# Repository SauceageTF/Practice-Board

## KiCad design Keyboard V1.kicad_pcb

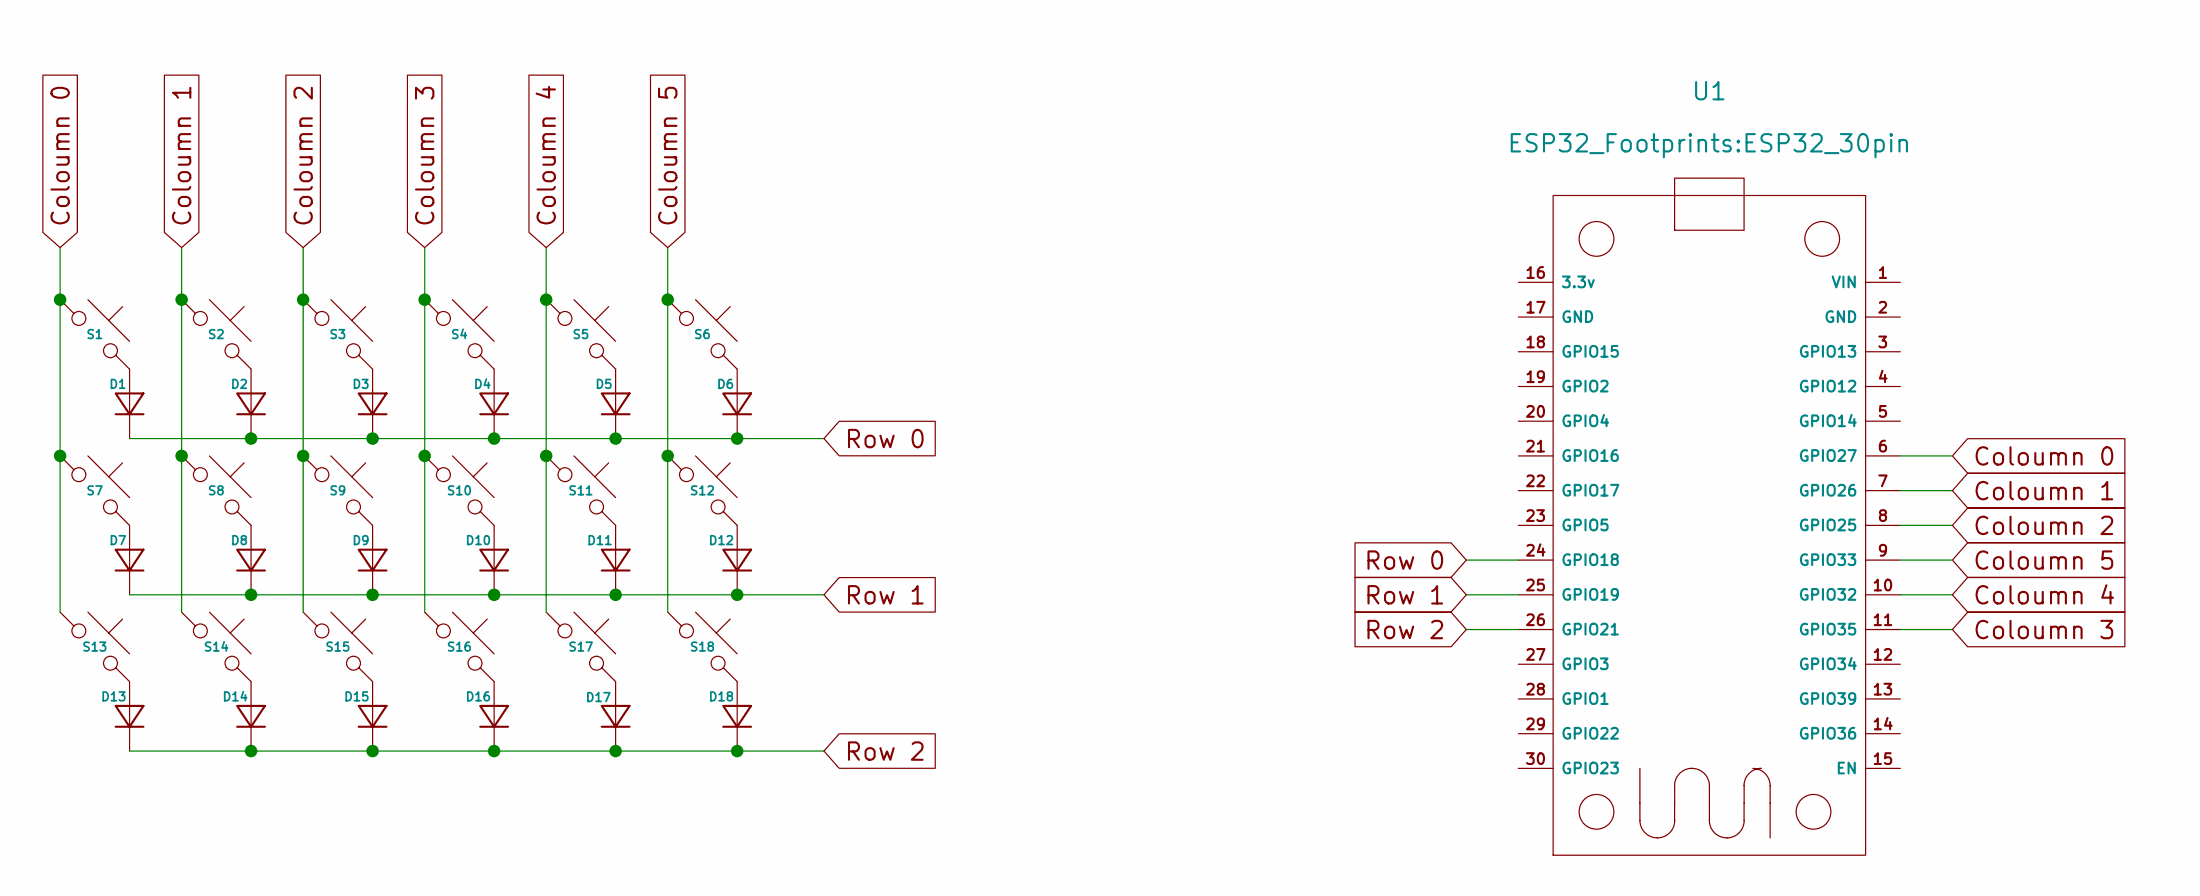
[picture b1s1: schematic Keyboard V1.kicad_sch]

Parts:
D1, D2, D3, D4, D5, D6, D7, D8, D9, D10, D11, D12, D13, D14, D15, D16, D17, D18: Diode_DO-35
S1, S2, S3, S4, S5, S6, S7, S8, S9, S10, S11, S12, S13, S14, S15, S16, S17, S18: MX_PCB_1.00u
U1: ESP32_30pin

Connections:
Coloumn 0: S1.1, S7.1, S13.1, U1.6 (GPIO27)
Coloumn 1: S2.1, S8.1, S14.1, U1.7 (GPIO26)
Coloumn 2: S3.1, S9.1, S15.1, U1.8 (GPIO25)
Coloumn 3: S4.1, S10.1, S16.1, U1.11 (GPIO35)
Coloumn 4: S5.1, S11.1, S17.1, U1.10 (GPIO32)
Coloumn 5: S6.1, S12.1, S18.1, U1.9 (GPIO33)
unnamed: D1.2 (A), S1.2
unnamed: D2.2 (A), S2.2
unnamed: D3.2 (A), S3.2
unnamed: D4.2 (A), S4.2
unnamed: D5.2 (A), S5.2
unnamed: D6.2 (A), S6.2
unnamed: D7.2 (A), S7.2
unnamed: D8.2 (A), S8.2
unnamed: D9.2 (A), S9.2
unnamed: D10.2 (A), S10.2
unnamed: D11.2 (A), S11.2
unnamed: D12.2 (A), S12.2
unnamed: D13.2 (A), S13.2
unnamed: D14.2 (A), S14.2
unnamed: D15.2 (A), S15.2
unnamed: D16.2 (A), S16.2
unnamed: D17.2 (A), S17.2
unnamed: D18.2 (A), S18.2
Row 0: D1.1 (K), D2.1 (K), D3.1 (K), D4.1 (K), D5.1 (K), D6.1 (K), U1.24 (GPIO18)
Row 1: D7.1 (K), D8.1 (K), D9.1 (K), D10.1 (K), D11.1 (K), D12.1 (K), U1.25 (GPIO19)
Row 2: D13.1 (K), D14.1 (K), D15.1 (K), D16.1 (K), D17.1 (K), D18.1 (K), U1.26 (GPIO21)

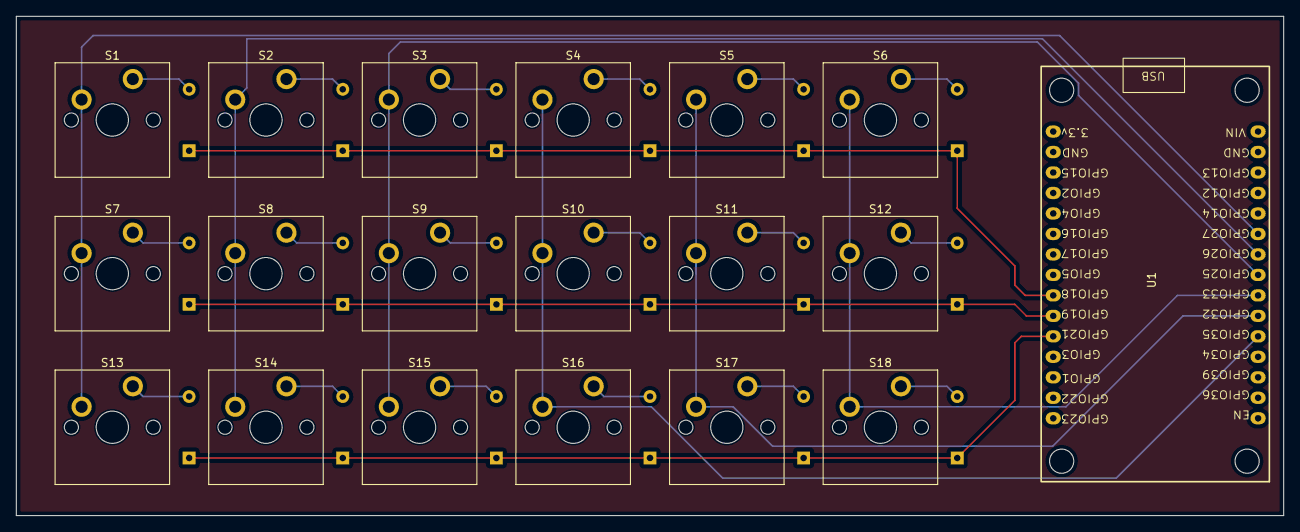
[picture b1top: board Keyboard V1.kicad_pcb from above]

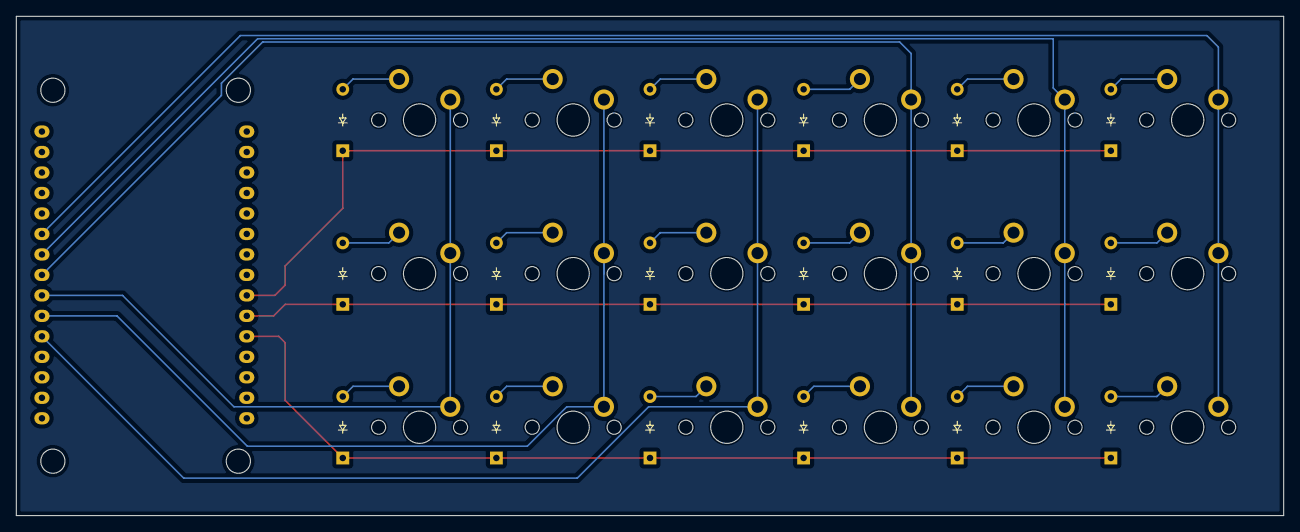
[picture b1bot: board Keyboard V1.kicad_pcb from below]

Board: 2 copper layers, 157.2 x 61.9 mm, 37 parts (18 on the bottom side), 27 nets.
